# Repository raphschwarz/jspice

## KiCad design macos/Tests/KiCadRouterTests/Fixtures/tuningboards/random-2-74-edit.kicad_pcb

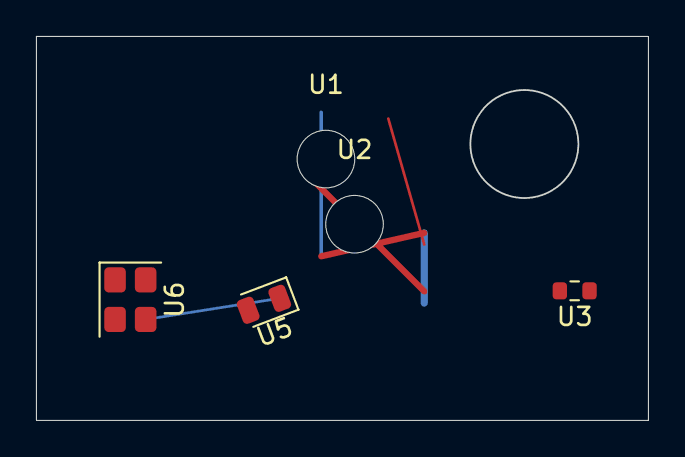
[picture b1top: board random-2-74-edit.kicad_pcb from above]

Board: 2 copper layers, 34.0 x 21.3 mm, 6 parts (1 on the bottom side), 5 nets.

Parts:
U1, U2: MountingHole_3.2mm_M3
U3: R_0603_1608Metric
U4: TSSOP-16_4.4x5mm_P0.65mm
U5: LED_0805_2012Metric
U6: Crystal_SMD_3225-4Pin_3.2x2.5mm

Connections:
/sub/clk: U6.1, U6.4
D7: U4.3, U4.5, U4.10, U5.2, U6.2
D12: U4.15, U5.1, U6.3
GND: U4.1, U4.14
N2: U4.4, U4.8, U4.11

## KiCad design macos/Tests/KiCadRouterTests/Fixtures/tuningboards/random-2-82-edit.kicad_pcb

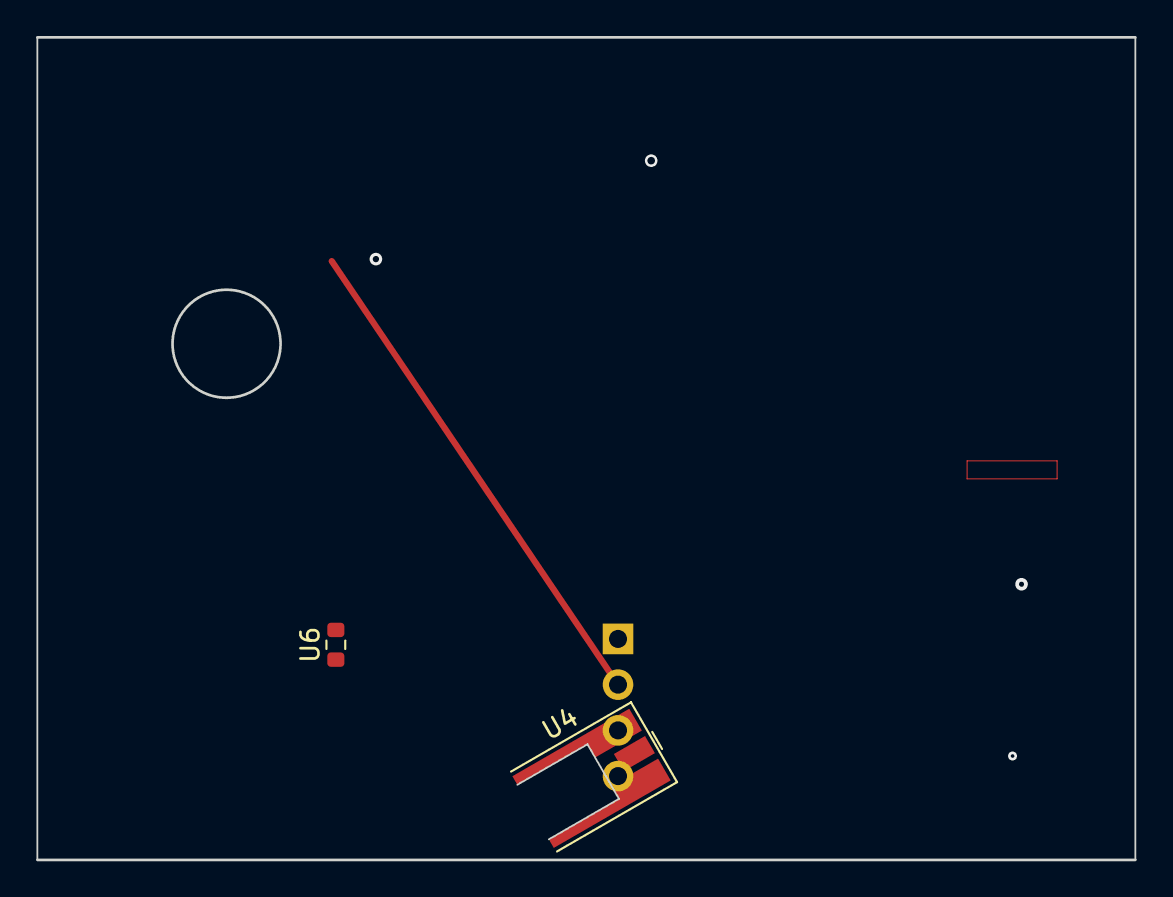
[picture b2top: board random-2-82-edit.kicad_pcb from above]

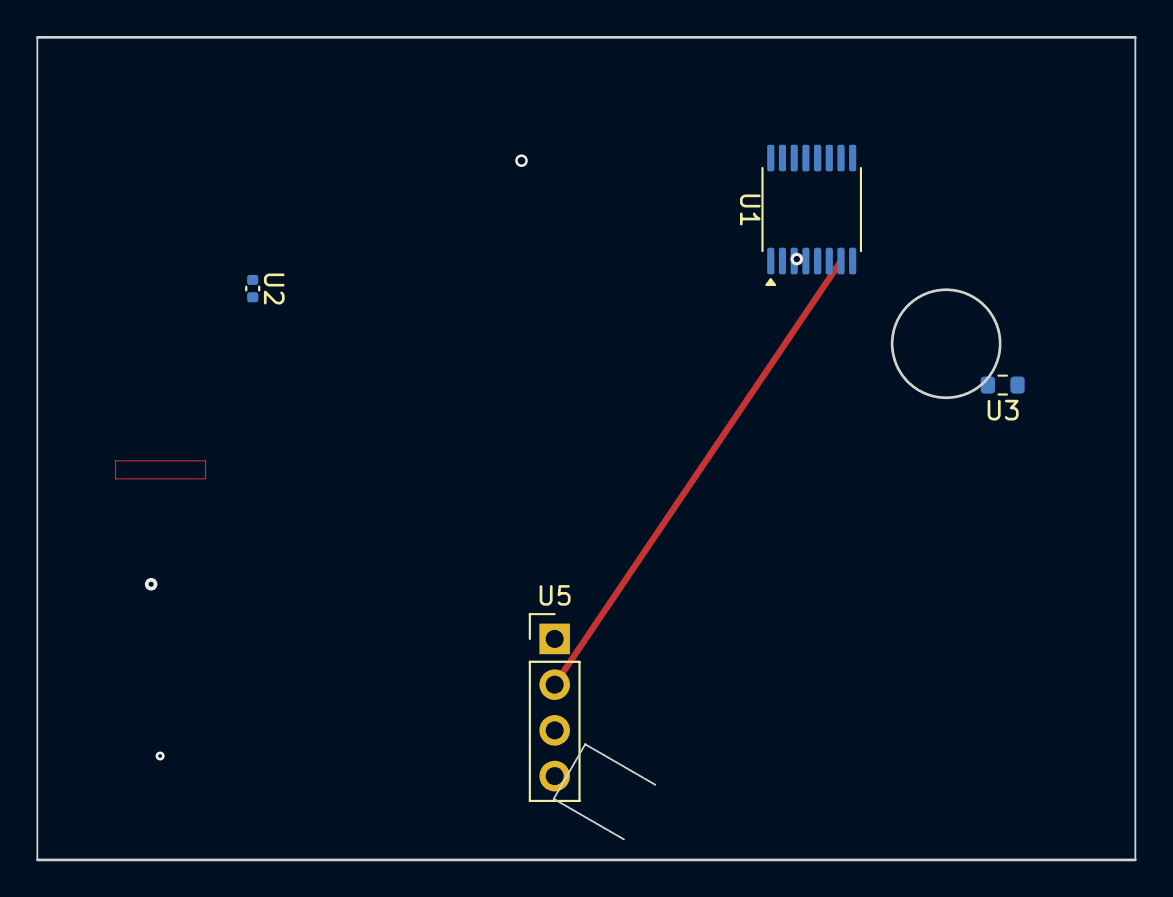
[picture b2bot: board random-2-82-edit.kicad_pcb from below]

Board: 4 copper layers, 61.0 x 45.7 mm, 6 parts (4 on the bottom side), 7 nets.

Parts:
U1: TSSOP-16_4.4x5mm_P0.65mm
U2: C_0402_1005Metric
U3, U6: R_0603_1608Metric
U4: MMCX_Molex_73415-0961_Horizontal_0.8mm-PCB
U5: PinHeader_1x04_P2.54mm_Vertical

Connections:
D7: U1.2, U1.11, U2.1
D12: U1.9, U6.1
GND: U1.7, U1.13, U3.1, U4.2, U5.3
N3: U1.3, U1.5
PWR1: U1.4, U5.1
PWR_5V: U1.6, U1.14, U1.16, U4.1, U5.4, U6.2
VCC: U1.1, U1.15, U2.2, U5.2

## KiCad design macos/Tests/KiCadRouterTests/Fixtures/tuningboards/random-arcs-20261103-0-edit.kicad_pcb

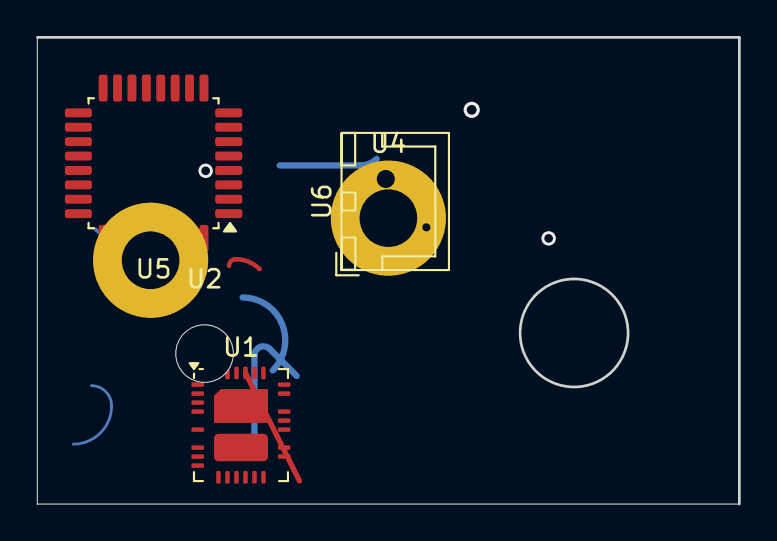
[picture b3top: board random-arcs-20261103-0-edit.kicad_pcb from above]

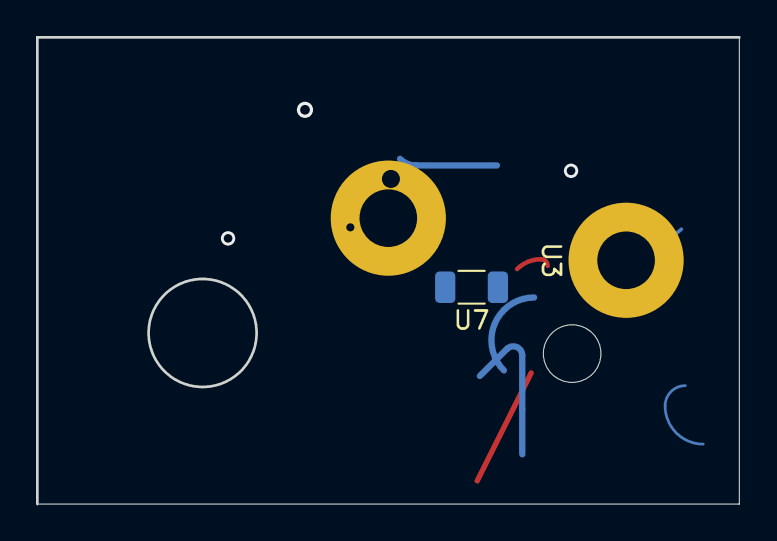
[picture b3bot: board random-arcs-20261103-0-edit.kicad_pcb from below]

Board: 2 copper layers, 39.0 x 25.9 mm, 7 parts (2 on the bottom side), 9 nets.

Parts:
U1: Analog_QFN-28-36-2EP_5x6mm_P0.5mm
U2: MountingHole_3.2mm_M3
U3, U4: MountingHole_3.2mm_M3_Pad
U5: LQFP-32_7x7mm_P0.8mm
U6: JST_XH_B2B-XH-A_1x02_P2.50mm_Vertical
U7: R_1206_3216Metric

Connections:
/sub/clk: U1.1, U1.14, U1.27, U5.1, U5.14, U5.18, U5.30
D7: U1.20, U1.24, U5.3, U5.11, U5.20
D12: U1.9, U5.21, U5.25
GND: U1.6, U1.21, U4.1, U5.2, U5.6
N1: U1.2, U1.10, U1.16, U1.36, U5.9, U5.13, U5.17, U5.19, U5.31, U6.1
N2: U1.37, U3.1, U5.12, U5.32, U7.2
N3: U1.33, U5.4, U5.10
PWR1: U1.17, U1.25, U1.28, U1.38, U5.8, U5.27, U5.29
SIG2: U1.13, U5.26, U7.1

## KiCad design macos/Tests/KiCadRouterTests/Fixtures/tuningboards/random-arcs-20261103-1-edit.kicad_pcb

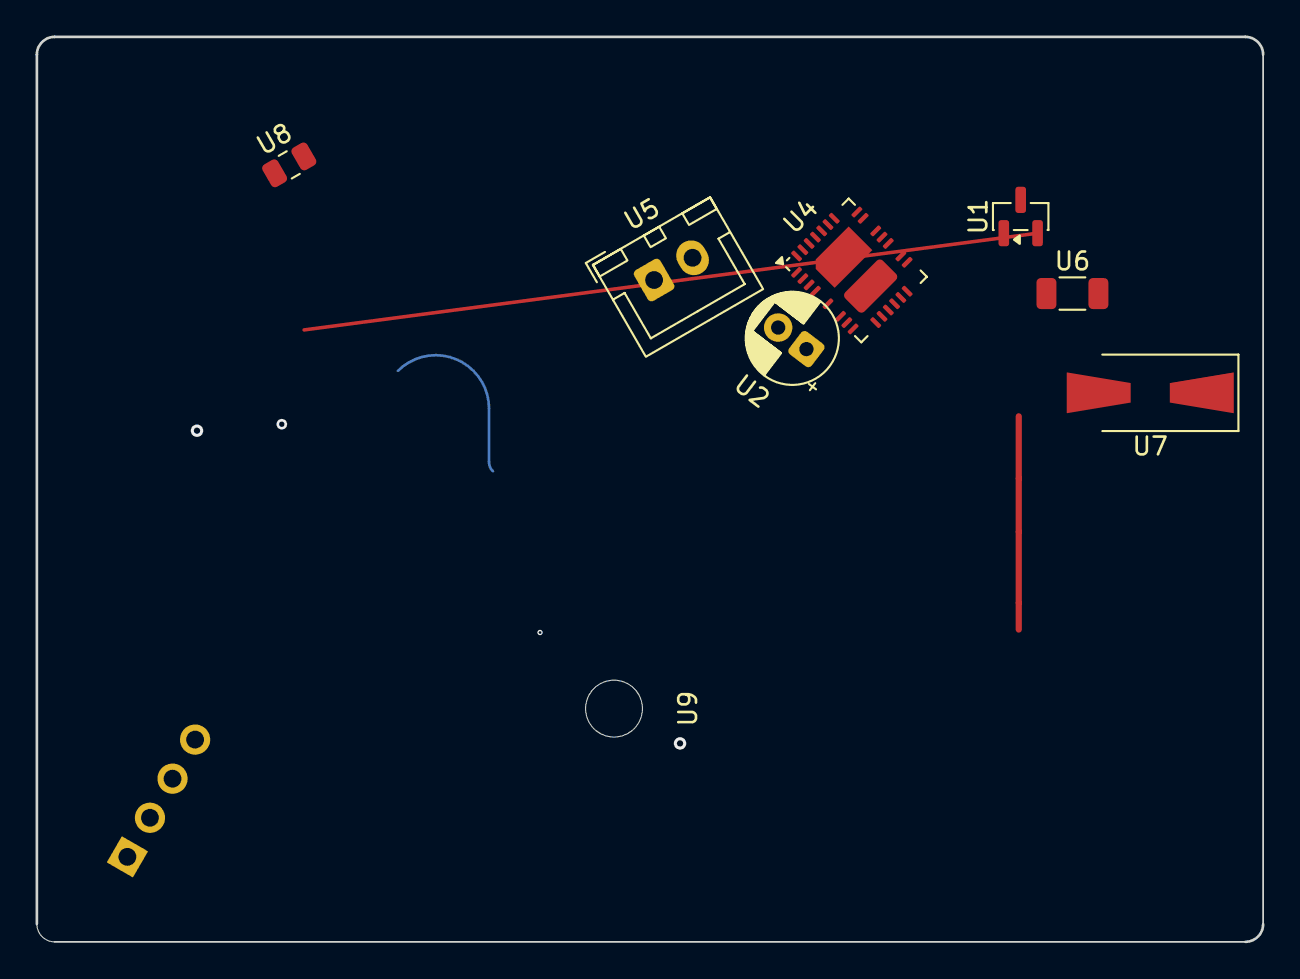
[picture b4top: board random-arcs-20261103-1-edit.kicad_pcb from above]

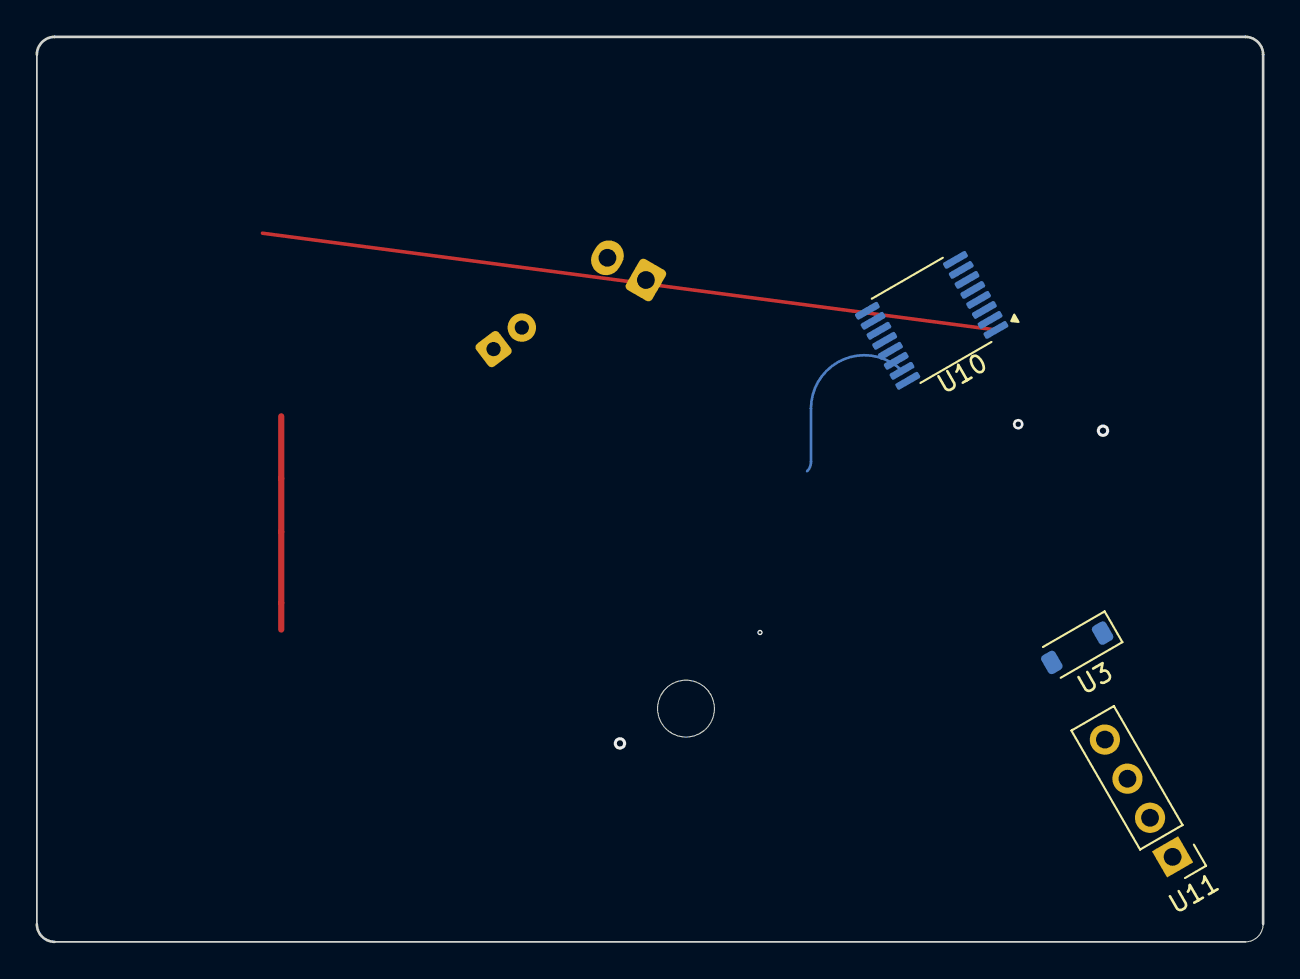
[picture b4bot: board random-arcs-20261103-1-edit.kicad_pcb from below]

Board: 4 copper layers, 69.0 x 50.9 mm, 11 parts (3 on the bottom side), 5 nets.

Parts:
U1: SOT-23
U2: CP_Radial_D5.0mm_P2.00mm
U3: D_SOD-123
U4: Analog_QFN-28-36-2EP_5x6mm_P0.5mm
U5: JST_XH_B2B-XH-A_1x02_P2.50mm_Vertical
U6: R_1206_3216Metric
U7: D_SMA-SMB_Universal_Handsoldering
U8: C_0805_2012Metric
U9: MountingHole_3.2mm_M3
U10: TSSOP-16_4.4x5mm_P0.65mm
U11: PinHeader_1x04_P2.54mm_Vertical

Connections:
/sub/clk: U1.1, U1.2, U3.1, U3.2, U4.1, U4.6, U4.21, U6.2, U11.1, U11.2
D7: U2.2, U4.10, U4.38, U6.1, U7.1, U10.2, U10.4, U10.8, U10.13
GND: U1.3, U2.1, U4.2, U4.13, U4.15, U4.16, U4.30, U5.1, U10.10, U10.11, U10.15, U10.16
SIG1: U4.9, U4.14, U4.17, U4.20, U4.24, U4.28, U4.32, U7.2, U10.6, U10.9
SIG2: U4.4, U4.12, U4.25, U4.31, U4.33, U4.34, U4.37, U5.2, U8.2, U10.5, U10.7
